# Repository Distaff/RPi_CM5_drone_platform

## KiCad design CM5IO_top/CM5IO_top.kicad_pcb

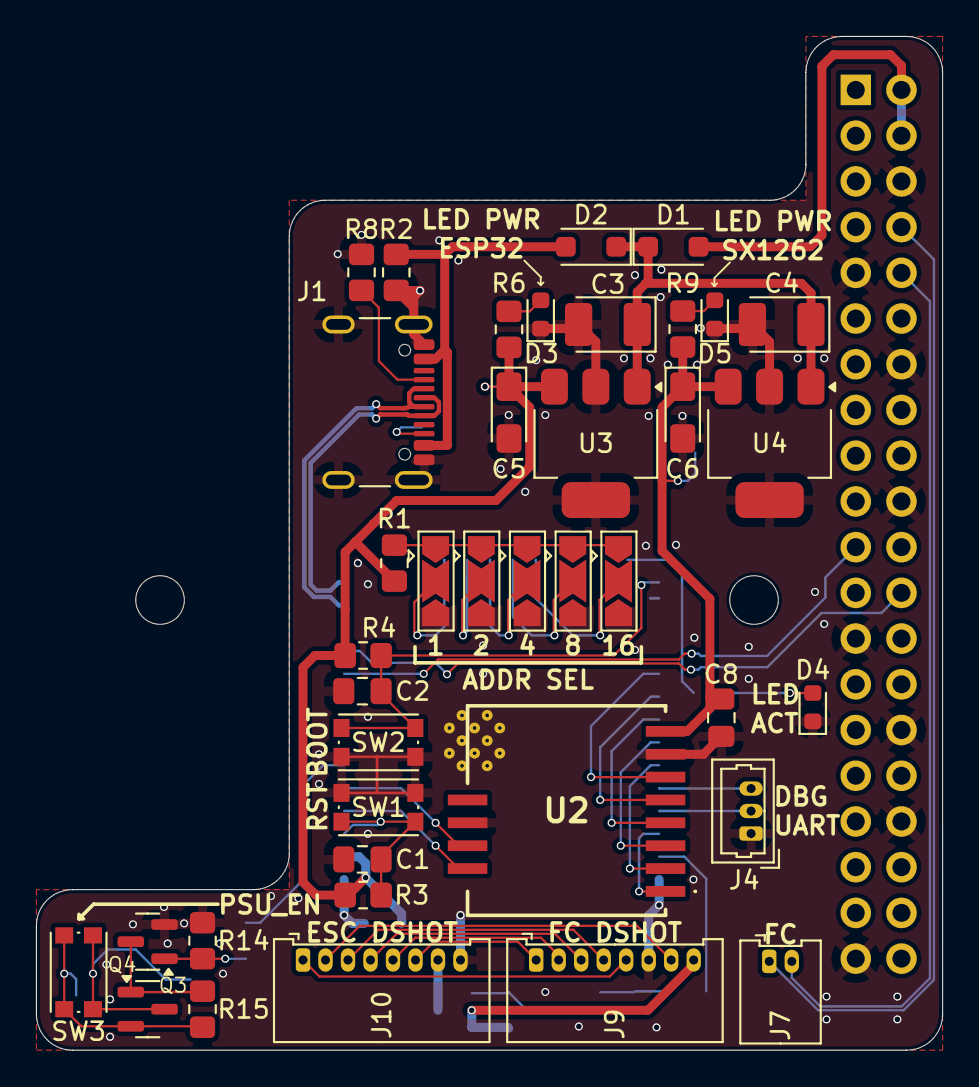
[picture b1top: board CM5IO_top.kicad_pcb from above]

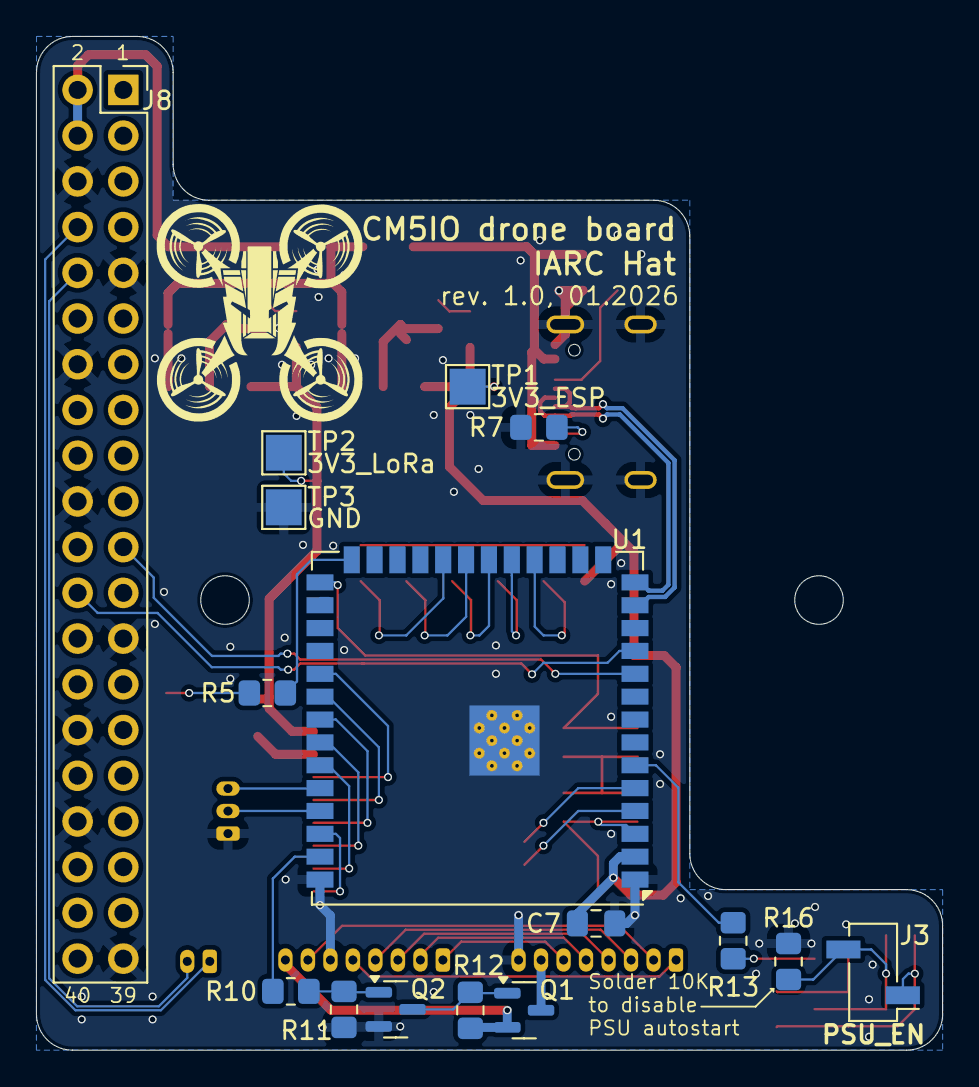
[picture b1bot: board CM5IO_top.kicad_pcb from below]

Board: 2 copper layers, 50.3 x 56.3 mm, 58 parts (16 on the bottom side), 52 nets.

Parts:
C1, C2, C7, C8: 470nF; C_0805_2012Metric_Pad1.18x1.45mm_HandSolder
C3, C4: 4.7uF 35v; CP_EIA-3528-21_Kemet-B_HandSolder
C5, C6: 4.7uF 10v; CP_EIA-3216-18_Kemet-A_HandSolder
D1, D2: MBR1020VL; D_SOD-123F
D3, D5: LED Red; LED_0603_1608Metric
D4: LED Green; LED_0603_1608Metric
H1, H2: MountingHole; MountingHole_2.7mm_M2.5_DIN965
J1: USB_C_Receptacle_USB2.0; USB_C_Receptacle_GCT_USB4105-xx-A_16P_TopMnt_Horizontal
J3: J_PSU_EN; PinSocket_1x02_P2.54mm_Vertical_SMD_Pin1Left
J4: J_ESP_DBG_UART; Molex_PicoBlade_53047-0310_1x03_P1.25mm_Vertical
J7: J_FC_UART; Molex_PicoBlade_53048-0210_1x02_P1.25mm_Horizontal
J8: THD-20-R; PinSocket_2x20_P2.54mm_Vertical
J9: J_DShot600_ESC; Molex_PicoBlade_53048-0810_1x08_P1.25mm_Horizontal
J10: J_DShot600_FC; Molex_PicoBlade_53048-0810_1x08_P1.25mm_Horizontal
JP1: ADDR1; SolderJumper-3_P2.0mm_Open_TrianglePad1.0x1.5mm
JP2: ADDR2; SolderJumper-3_P2.0mm_Open_TrianglePad1.0x1.5mm
JP3: ADDR4; SolderJumper-3_P2.0mm_Open_TrianglePad1.0x1.5mm
JP4: ADDR8; SolderJumper-3_P2.0mm_Open_TrianglePad1.0x1.5mm
JP5: ADDR16; SolderJumper-3_P2.0mm_Open_TrianglePad1.0x1.5mm
Module1: ComputeModule5-CM5; Raspberry-Pi-5-Compute-Module
Q1, Q4: AO3401A; SOT-23
Q2, Q3: Q_NPN_BEC; SOT-23
R1, R3, R4, R5, R6, R9, R10, R12, R13, R15: 1K; R_0805_2012Metric_Pad1.20x1.40mm_HandSolder
R2: 2.2K 1%; R_0805_2012Metric_Pad1.20x1.40mm_HandSolder
R7, R8: 5.1K 1%; R_0805_2012Metric_Pad1.20x1.40mm_HandSolder
R11, R14, R16: 10K; R_0805_2012Metric_Pad1.20x1.40mm_HandSolder
SW1: SW_RESET; SW_Push_1P1T_NO_CK_KMR2
SW2: SW_BOOT; SW_Push_1P1T_NO_CK_KMR2
SW3: FORCE_PWR; SW_Push_1P1T_NO_CK_KMR2
TP1: 3V3_ESP; TestPoint_Pad_2.0x2.0mm
TP2: 3V3_LORA; TestPoint_Pad_2.0x2.0mm
TP3: GND; TestPoint_Pad_2.0x2.0mm
U1: ESP32-S3-WROOM-1; ESP32-S3-WROOM-1U
U2: Wio-SX1262
U3, U4: AP7361C-33E; SOT-223-3_TabPin2

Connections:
/+3.3v_ESP: C5.1, C7.2, R1.1, R3.1, R4.1, R6.1, TP1.1, U1.2 (3V3), U3.3 (VO)
/+3.3v_LoRa: C6.1, C8.2, R9.1, TP2.1, U2.8 (VCC), U4.3 (VO)
/+5v_RPi: D1.2 (A), J8.2, J8.4
/+5v_USB: D2.2 (A), J1.A4 (VBUS), J1.A9 (VBUS), J1.B4 (VBUS), J1.B9 (VBUS), R2.1
/Comm/ADDR1: JP1.2 (C), U1.18 (IO10)
/Comm/ADDR2: JP2.2 (C), U1.19 (IO11)
/Comm/ADDR4: JP3.2 (C), U1.20 (IO12)
/Comm/ADDR8: JP4.2 (C), U1.21 (IO13)
/Comm/ADDR16: JP5.2 (C), U1.22 (IO14)
/Comm/ADDR_HIGH: JP1.1 (A), JP2.1 (A), JP3.1 (A), JP4.1 (A), JP5.1 (A), R1.2
/Comm/BOOT_MODE: C2.2, R4.2, SW2.2, U1.27 (IO0)
/Comm/ENABLE: C1.2, R3.2, SW1.2, U1.3 (EN)
/Comm/KILLSWITCH_FC_CTL: R10.1, U1.39 (IO1)
/Comm/KILLSWITCH_PSU_CTL: R13.1, U1.6 (IO6)
/Comm/LED_ACT: R5.1, U1.26 (IO45)
/Comm/LORA_BUSY: U1.5 (IO5), U2.11 (BUSY)
/Comm/LORA_DIO1: U1.4 (IO4), U2.12 (DIO1)
/Comm/LORA_RESET: U1.32 (IO39), U2.5 (NRST)
/Comm/LORA_RF_SW: U1.38 (IO2), U2.1 (RF_SW_)
/Comm/LORA_SPI_CLK: U1.33 (IO40), U2.4 (SCK)
/Comm/LORA_SPI_CS: U1.31 (IO38), U2.6 (NSS)
/Comm/LORA_SPI_MISO: U1.35 (IO42), U2.2 (MISO)
/Comm/LORA_SPI_MOSI: U1.34 (IO41), U2.3 (MOSI)
/Dshot600_CURR: J9.5, J10.1
/Dshot600_M1: J9.4, J10.3
/Dshot600_M2: J9.3, J10.4
/Dshot600_M3: J9.2, J10.5
/Dshot600_M4: J9.1, J10.6
/Dshot600_R7: J9.7, J10.2
/ESP_USB2_N: J1.A7 (D-), J1.B7 (D-), U1.13 (USB_D-)
/ESP_USB2_P: J1.A6 (D+), J1.B6 (D+), U1.14 (USB_D+)
/GPIO8: J8.24, U1.11 (IO18)
/GPIO9: J8.21, U1.10 (IO17)
/GPIO14_UART_TX: J7.1, J8.8
/GPIO15_UART_RX: J7.2, J8.10
/PSU_CTL_EN: J3.2, Q4.3 (D), R16.1, SW3.1
/PSU_VIN: J3.1, Q4.2 (S), R15.1, SW3.2
/VBUS_ESC: J9.8, Q1.2 (S), R12.1
/VBUS_FC: J10.7, Q1.3 (D)
/VIN: C3.1, C4.1, D1.1 (K), D2.1 (K), U3.1 (VI), U4.1 (VI)
GND: C1.1, C2.1, C3.2, C4.2, C5.2, C6.2, C7.1, C8.1, D3.1 (K), D4.1 (K), D5.1 (K), J1.A1 (GND), J1.A12 (GND), J1.B1 (GND), J1.B12 (GND), J1.S1 (SHIELD), J4.1, J8.6, J8.9, J8.14, J8.20, J8.25, J8.30, J8.34, J8.39, J9.6, J10.8, JP1.3 (B), JP2.3 (B), JP3.3 (B), JP4.3 (B), JP5.3 (B), Q2.2 (E), Q3.2 (E), R2.2, R7.1, R8.1, R11.2, R14.2, R16.2, SW1.1, SW2.1, TP3.1, U1.1 (GND), U1.40 (GND), U1.41 (GND), U2.7 (GND_1), U2.10 (GND_2), U3.2 (GND), U4.2 (GND)
unnamed: D3.2 (A), R6.2
unnamed: D4.2 (A), R5.2
unnamed: D5.2 (A), R9.2
unnamed: J1.A5 (CC1), R8.2
unnamed: J1.B5 (CC2), R7.2
unnamed: J4.2, U1.37 (TXD0)
unnamed: J4.3, U1.36 (RXD0)
unnamed: Q1.1 (G), Q2.3 (C), R12.2
unnamed: Q2.1 (B), R10.2, R11.1
unnamed: Q3.1 (B), R13.2, R14.1
unnamed: Q3.3 (C), Q4.1 (G), R15.2

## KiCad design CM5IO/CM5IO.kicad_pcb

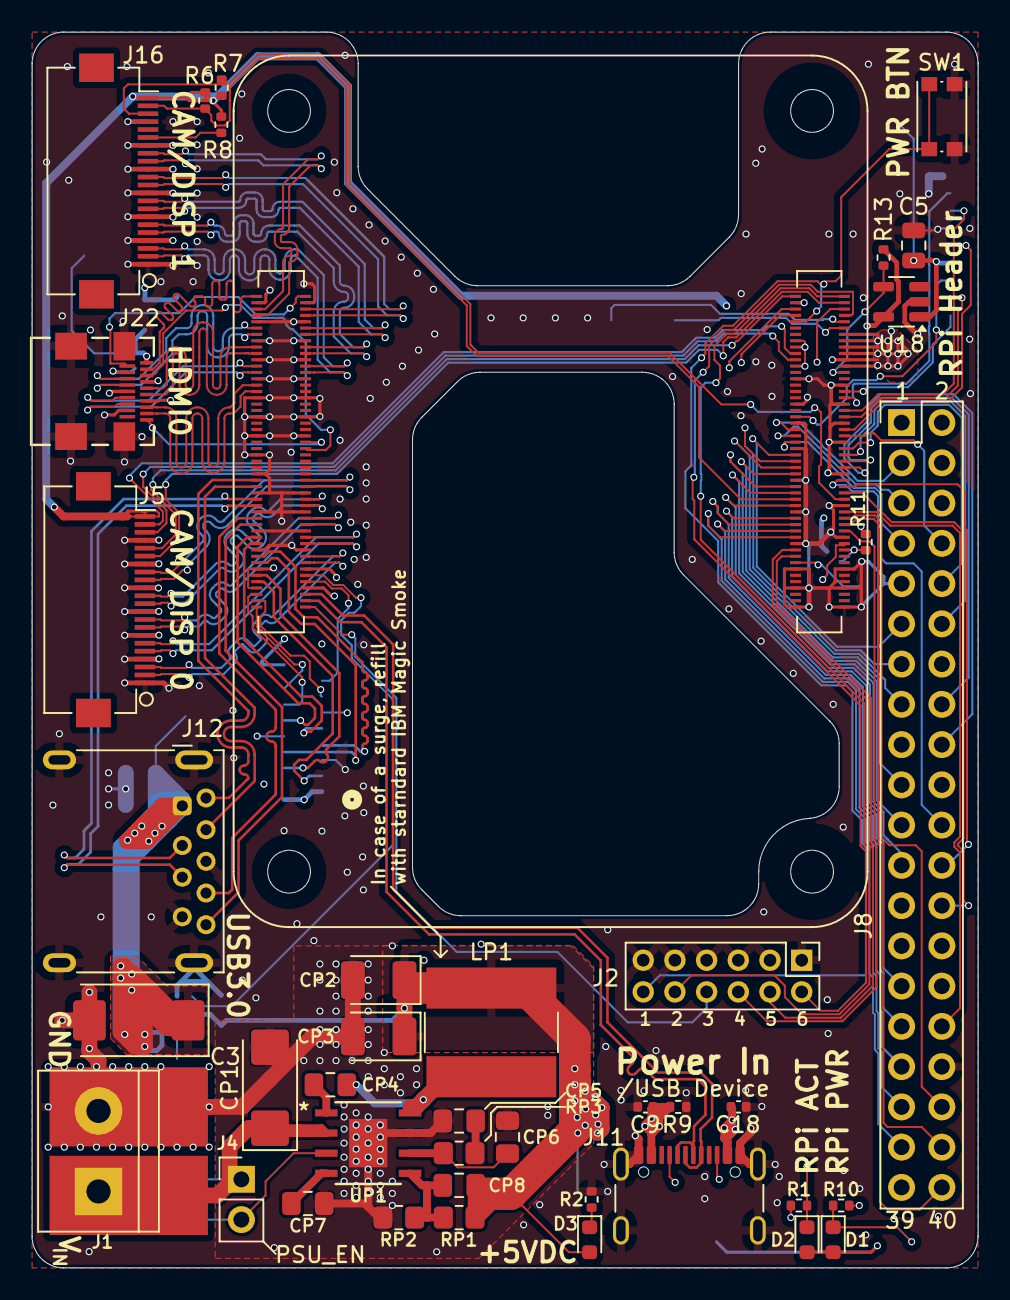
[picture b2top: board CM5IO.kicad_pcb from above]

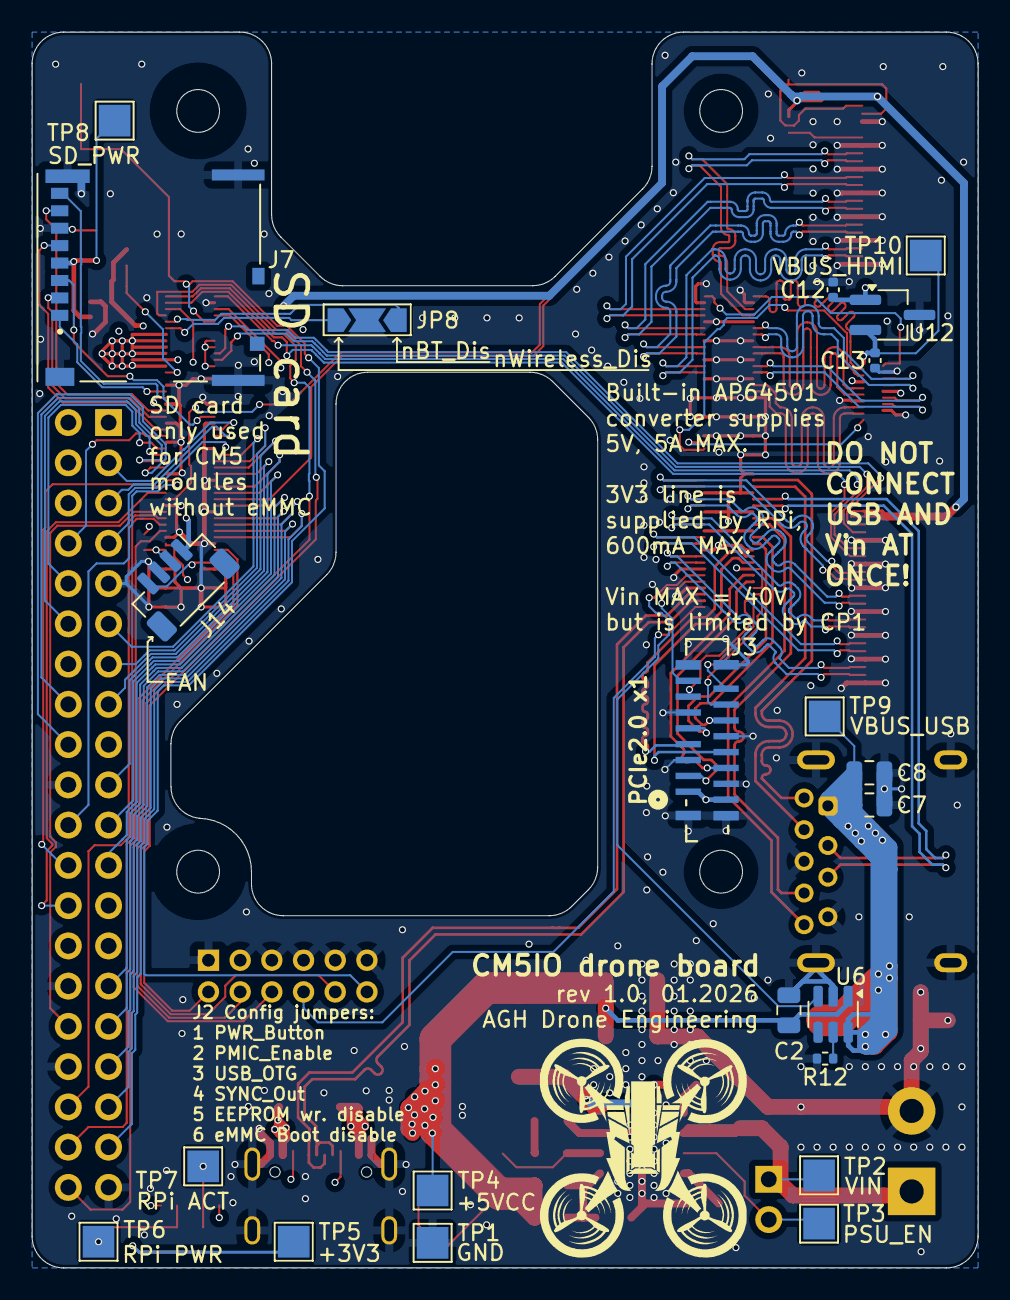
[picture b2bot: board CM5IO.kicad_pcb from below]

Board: 4 copper layers, 59.7 x 78.0 mm, 65 parts (22 on the bottom side), 123 nets.

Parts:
C2, C5, C7, C8: 10u; C_0805_2012Metric
C3: 100uF; CP_EIA-7343-31_Kemet-D
C9, C12, C13, C18: 100n; C_0402_1005Metric
CP1: 10uF; CP_EIA-6032-28_Kemet-C_HandSolder
CP2, CP3: 22uF; CP_EIA-3528-21_Kemet-B_HandSolder
CP4: 100nF; C_0805_2012Metric_Pad1.18x1.45mm_HandSolder
CP5: 2.7nF; C_0805_2012Metric_Pad1.18x1.45mm_HandSolder
CP6: 33pF; C_0805_2012Metric_Pad1.18x1.45mm_HandSolder
CP7: 10nF; C_0805_2012Metric_Pad1.18x1.45mm_HandSolder
CP8: OPEN; C_0805_2012Metric_Pad1.18x1.45mm_HandSolder
D1, D3: LED Red; LED_0603_1608Metric
D2: LED Green; LED_0603_1608Metric
H9: VIN_SOLDERPOINT; SolderWirePad_1x01_SMD_5x10mm
H10: GND_SOLDERPOINT; SolderWirePad_1x01_SMD_5x10mm
J1: POWER TERMINAL; TerminalBlock_bornier-2_P5.08mm
J2: Conn_02x06_Odd_Even; PinHeader_2x06_P2.00mm_Vertical
J3: 62674-161121ALF; CON16_1X16_DUT_58XF_GLE
J4: J_PSU_EN; PinHeader_1x02_P2.54mm_Vertical
J5, J16: Conn_01x22_Female; Hirose_FH12-22S-0.5SH_1x22-1MP_P0.50mm_Horizontal
J7: Micro_SD_Card_Det; SDCARD_MOLEX_503398-1892
J8: THD-20-R; PinHeader_2x20_P2.54mm_Vertical
J11: USB_C_Receptacle_USB2.0; USB_C_Receptacle_GCT_USB4105-xx-A_16P_TopMnt_Horizontal
J12: USB3_A; USB3_A_Molex_48393-001
J14: JST_SHBM04B-SRSS-TB; JST_SH_BM04B-SRSS-TB_1x04-1MP_P1.00mm_Vertical
J22: 46765-1301; CONN_467651301_MOL
JP8: BT_WIFI_DISABLE; SolderJumper-3_P2.0mm_Open_TrianglePad1.0x1.5mm
LP1: 3.6uH; L_Bourns-SRN8040_8x8.15mm
Module1: ComputeModule5-CM5; Raspberry-Pi-5-Compute-Module
R1, R2, R10: 1k; R_0402_1005Metric
R6, R7, R8, R9: 2.2K 1%; R_0402_1005Metric
R11, R13: 10K 1%; R_0402_1005Metric
R12: 15K 1%; R_0402_1005Metric
RP1: 115K; R_0805_2012Metric_Pad1.20x1.40mm_HandSolder
RP2: 22.1K; R_0805_2012Metric_Pad1.20x1.40mm_HandSolder
RP3: 15.8K; R_0805_2012Metric_Pad1.20x1.40mm_HandSolder
SW1: Right angle Tact button; SW_Push_1P1T_NO_CK_KMR2
TP1: TP GND; TestPoint_Pad_2.0x2.0mm
TP2: TP VIN; TestPoint_Pad_2.0x2.0mm
TP3: TP PSU_EN; TestPoint_Pad_2.0x2.0mm
TP4: TP +5VCC; TestPoint_Pad_2.0x2.0mm
TP5: TP +3V3; TestPoint_Pad_2.0x2.0mm
TP6: TP nPWR; TestPoint_Pad_2.0x2.0mm
TP7: TP nACT; TestPoint_Pad_2.0x2.0mm
TP8: TP SD_PWR; TestPoint_Pad_2.0x2.0mm
TP9: TP VBUS_USB; TestPoint_Pad_2.0x2.0mm
TP10: TP VBUS_HDMI; TestPoint_Pad_2.0x2.0mm
U6: AP22653W6; SOT-23-6
U12: RT9742SNGV; TSOT-23_HandSoldering
U18: RT9742GGJ5; SOT-23-5
UP1: AP64501SP-13; SOP_AP64501SP-13_DIO

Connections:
/+3.3v: D1.2 (A), D2.2 (A), J5.22, J8.1, J8.17, J16.22, Module1.78 (GPIO_VREF(1.8v/3.3v_Input)), Module1.84 (+3.3v_(Output)), Module1.86 (+3.3v_(Output)), R6.1, R7.1, R8.1, R11.1, R13.1, TP5.1, U18.5 (IN)
/+5v: C2.1, C9.1, C12.1, C18.1, CP2.1, CP3.1, CP8.1, D3.2 (A), J3.1, J3.2, J8.2, J8.4, J11.A4 (VBUS), J11.A9 (VBUS), J11.B4 (VBUS), J11.B9 (VBUS), J14.1, LP1.2, Module1.77 (+5v_(Input)), Module1.79 (+5v_(Input)), Module1.81 (+5v_(Input)), Module1.83 (+5v_(Input)), Module1.85 (+5v_(Input)), Module1.87 (+5v_(Input)), R9.1, RP1.1, TP4.1, U6.1 (IN), U12.1 (IN)
/CC1: J11.A5 (CC1), Module1.94 (CC1)
/CC2: J11.B5 (CC2), Module1.96 (CC2)
/CM5_GPIO ( Ethernet, GPIO, SDCARD)/BT_nDis: JP8.3 (B), Module1.91 (BT_nDisable)
/CM5_GPIO ( Ethernet, GPIO, SDCARD)/CAM_GPIO0: J5.17, Module1.97 (CAM_GPIO0)
/CM5_GPIO ( Ethernet, GPIO, SDCARD)/CAM_GPIO1: J5.18, Module1.100 (CAM_GPIO1)
/CM5_GPIO ( Ethernet, GPIO, SDCARD)/EEPROM_nWP: J2.4, Module1.20 (EEPROM_nWP)
/CM5_GPIO ( Ethernet, GPIO, SDCARD)/GPIO2: J8.3, Module1.58 (GPIO2)
/CM5_GPIO ( Ethernet, GPIO, SDCARD)/GPIO3: J8.5, Module1.56 (GPIO3)
/CM5_GPIO ( Ethernet, GPIO, SDCARD)/GPIO4: J8.7, Module1.54 (GPIO4)
/CM5_GPIO ( Ethernet, GPIO, SDCARD)/GPIO5: J8.29, Module1.34 (GPIO5)
/CM5_GPIO ( Ethernet, GPIO, SDCARD)/GPIO6: J8.31, Module1.30 (GPIO6)
/CM5_GPIO ( Ethernet, GPIO, SDCARD)/GPIO7: J8.26, Module1.37 (GPIO7)
/CM5_GPIO ( Ethernet, GPIO, SDCARD)/GPIO8: J8.24, Module1.39 (GPIO8)
/CM5_GPIO ( Ethernet, GPIO, SDCARD)/GPIO9: J8.21, Module1.40 (GPIO9)
/CM5_GPIO ( Ethernet, GPIO, SDCARD)/GPIO10: J8.19, Module1.44 (GPIO10)
/CM5_GPIO ( Ethernet, GPIO, SDCARD)/GPIO11: J8.23, Module1.38 (GPIO11)
/CM5_GPIO ( Ethernet, GPIO, SDCARD)/GPIO12: J8.32, Module1.31 (GPIO12)
/CM5_GPIO ( Ethernet, GPIO, SDCARD)/GPIO13: J8.33, Module1.28 (GPIO13)
/CM5_GPIO ( Ethernet, GPIO, SDCARD)/GPIO14: J8.8, Module1.55 (GPIO14)
/CM5_GPIO ( Ethernet, GPIO, SDCARD)/GPIO15: J8.10, Module1.51 (GPIO15)
/CM5_GPIO ( Ethernet, GPIO, SDCARD)/GPIO16: J8.36, Module1.29 (GPIO16)
/CM5_GPIO ( Ethernet, GPIO, SDCARD)/GPIO17: J8.11, Module1.50 (GPIO17)
/CM5_GPIO ( Ethernet, GPIO, SDCARD)/GPIO18: J8.12, Module1.49 (GPIO18)
/CM5_GPIO ( Ethernet, GPIO, SDCARD)/GPIO19: J8.35, Module1.26 (GPIO19)
/CM5_GPIO ( Ethernet, GPIO, SDCARD)/GPIO20: J8.38, Module1.27 (GPIO20)
/CM5_GPIO ( Ethernet, GPIO, SDCARD)/GPIO21: J8.40, Module1.25 (GPIO21)
/CM5_GPIO ( Ethernet, GPIO, SDCARD)/GPIO22: J8.15, Module1.46 (GPIO22)
/CM5_GPIO ( Ethernet, GPIO, SDCARD)/GPIO23: J8.16, Module1.47 (GPIO23)
/CM5_GPIO ( Ethernet, GPIO, SDCARD)/GPIO24: J8.18, Module1.45 (GPIO24)
/CM5_GPIO ( Ethernet, GPIO, SDCARD)/GPIO25: J8.22, Module1.41 (GPIO25)
/CM5_GPIO ( Ethernet, GPIO, SDCARD)/GPIO26: J8.37, Module1.24 (GPIO26)
/CM5_GPIO ( Ethernet, GPIO, SDCARD)/GPIO27: J8.13, Module1.48 (GPIO27)
/CM5_GPIO ( Ethernet, GPIO, SDCARD)/PMIC_ENABLE: J2.10, Module1.99 (PMIC_ENABLE)
/CM5_GPIO ( Ethernet, GPIO, SDCARD)/PWM: J14.2, Module1.19 (FAN_PWM), R11.2
/CM5_GPIO ( Ethernet, GPIO, SDCARD)/PWR_BUT: J2.12, Module1.92 (PWR_BUT), SW1.1
/CM5_GPIO ( Ethernet, GPIO, SDCARD)/SD_CLK: J7.5 (CLK), Module1.57 (SD_CLK)
/CM5_GPIO ( Ethernet, GPIO, SDCARD)/SD_CMD: J7.3 (CMD), Module1.62 (SD_CMD)
/CM5_GPIO ( Ethernet, GPIO, SDCARD)/SD_DAT0: J7.7 (DAT0), Module1.63 (SD_DAT0)
/CM5_GPIO ( Ethernet, GPIO, SDCARD)/SD_DAT1: J7.8 (DAT1), Module1.67 (SD_DAT1)
/CM5_GPIO ( Ethernet, GPIO, SDCARD)/SD_DAT2: J7.1 (DAT2), Module1.69 (SD_DAT2)
/CM5_GPIO ( Ethernet, GPIO, SDCARD)/SD_DAT3: J7.2 (DAT3/CD), Module1.61 (SD_DAT3)
/CM5_GPIO ( Ethernet, GPIO, SDCARD)/SD_PWR: C5.1, J7.4 (VDD), TP8.1, U18.1 (OUT)
/CM5_GPIO ( Ethernet, GPIO, SDCARD)/SD_PWR_ON: Module1.75 (SD_PWR_ON), R13.2, U18.4 (EN)
/CM5_GPIO ( Ethernet, GPIO, SDCARD)/SYNC_OUT: J2.6, Module1.18 (Ethernet_SYNC_OUT(3.3v))
/CM5_GPIO ( Ethernet, GPIO, SDCARD)/TACHO: J14.4, Module1.16 (FAN_TACHO)
/CM5_GPIO ( Ethernet, GPIO, SDCARD)/USBOTG: J2.8, Module1.101 (USB_OTG_ID)
/CM5_GPIO ( Ethernet, GPIO, SDCARD)/WL_nDis: JP8.1 (A), Module1.89 (WiFi_nDisable)
/CM5_GPIO ( Ethernet, GPIO, SDCARD)/nPWR_LED: Module1.95 (LED_nPWR), R10.2
/CM5_GPIO ( Ethernet, GPIO, SDCARD)/nRPIBOOT: J2.2, Module1.93 (nRPIBOOT)
/CM5_HighSpeed/DPHY0_C_N: J5.8, Module1.127 (MIPI0_C_N)
/CM5_HighSpeed/DPHY0_C_P: J5.9, Module1.129 (MIPI0_C_P)
/CM5_HighSpeed/DPHY0_D0_N: J5.2, Module1.115 (MIPI0_D0_N)
/CM5_HighSpeed/DPHY0_D0_P: J5.3, Module1.117 (MIPI0_D0_P)
/CM5_HighSpeed/DPHY0_D1_N: J5.5, Module1.121 (MIPI0_D1_N)
/CM5_HighSpeed/DPHY0_D1_P: J5.6, Module1.123 (MIPI0_D1_P)
/CM5_HighSpeed/DPHY0_D2_N: J5.11, Module1.133 (MIPI0_D2_N)
/CM5_HighSpeed/DPHY0_D2_P: J5.12, Module1.135 (MIPI0_D2_P)
/CM5_HighSpeed/DPHY0_D3_N: J5.14, Module1.139 (MIPI0_D3_N)
/CM5_HighSpeed/DPHY0_D3_P: J5.15, Module1.141 (MIPI0_D3_P)
/CM5_HighSpeed/DPHY1_C_N: J16.8, Module1.187 (MIPI1_C_N)
/CM5_HighSpeed/DPHY1_C_P: J16.9, Module1.189 (MIPI1_C_P)
/CM5_HighSpeed/DPHY1_D0_N: J16.2, Module1.175 (MIPI1_D0_N)
/CM5_HighSpeed/DPHY1_D0_P: J16.3, Module1.177 (MIPI1_D0_P)
/CM5_HighSpeed/DPHY1_D1_N: J16.5, Module1.181 (MIPI1_D1_N)
/CM5_HighSpeed/DPHY1_D1_P: J16.6, Module1.183 (MIPI1_D1_P)
/CM5_HighSpeed/DPHY1_D2_N: J16.11, Module1.193 (MIPI1_D2_N)
/CM5_HighSpeed/DPHY1_D2_P: J16.12, Module1.195 (MIPI1_D2_P)
/CM5_HighSpeed/DPHY1_D3_N: J16.14, Module1.194 (MIPI1_D3_N)
/CM5_HighSpeed/DPHY1_D3_P: J16.15, Module1.196 (MIPI1_D3_P)
/CM5_HighSpeed/HDMI0_CEC: J22.15 (CEC), Module1.151 (HDMI0_CEC)
/CM5_HighSpeed/HDMI0_CK_N: J22.14 (CK-), Module1.190 (HDMI0_CLK_N)
/CM5_HighSpeed/HDMI0_CK_P: J22.12 (CK+), Module1.188 (HDMI0_CLK_P)
/CM5_HighSpeed/HDMI0_D0_N: J22.11 (D0-), Module1.184 (HDMI0_TX0_N)
/CM5_HighSpeed/HDMI0_D0_P: J22.9 (D0+), Module1.182 (HDMI0_TX0_P)
/CM5_HighSpeed/HDMI0_D1_N: J22.8 (D1-), Module1.178 (HDMI0_TX1_N)
/CM5_HighSpeed/HDMI0_D1_P: J22.6 (D1+), Module1.176 (HDMI0_TX1_P)
/CM5_HighSpeed/HDMI0_D2_N: J22.5 (D2-), Module1.172 (HDMI0_TX2_N)
/CM5_HighSpeed/HDMI0_D2_P: J22.3 (D2+), Module1.170 (HDMI0_TX2_P)
/CM5_HighSpeed/HDMI0_HOTPLUG: J22.1 (HPD/HEAC-), Module1.153 (HDMI0_HOTPLUG)
/CM5_HighSpeed/HDMI0_SCL: J22.17 (SCL), Module1.200 (HDMI0_SCL)
/CM5_HighSpeed/HDMI0_SDA: J22.18 (SDA), Module1.199 (HDMI0_SDA)
/CM5_HighSpeed/HDMI_5v: C13.1, J22.19 (+5V), TP10.1, U12.2 (OUT)
/CM5_HighSpeed/PCIE_CLKREQ_N: J3.15, Module1.102 (PCIe_nCLKREQ)
/CM5_HighSpeed/PCIE_CLK_N: J3.5, Module1.112 (PCIe_CLK_N)
/CM5_HighSpeed/PCIE_CLK_P: J3.4, Module1.110 (PCIe_CLK_P)
/CM5_HighSpeed/PCIE_DET_WAKE: J3.14, Module1.104 (PCIE_nWAKE)
/CM5_HighSpeed/PCIE_PWR_EN: J3.13, Module1.106 (PCIE_PWR_EN)
/CM5_HighSpeed/PCIE_RST_B: J3.16, Module1.109 (PCIe_nRST)
/CM5_HighSpeed/PCIE_RX_N: J3.8, Module1.118 (PCIe_RX_N)
/CM5_HighSpeed/PCIE_RX_P: J3.7, Module1.116 (PCIe_RX_P)
/CM5_HighSpeed/PCIE_TX_N: J3.11, Module1.124 (PCIe_TX_N)
/CM5_HighSpeed/PCIE_TX_P: J3.10, Module1.122 (PCIe_TX_P)
/CM5_HighSpeed/SCL0: J5.20, Module1.80 (SCL0)
/CM5_HighSpeed/SCL1: J16.20, Module1.35 (ID_SC), R7.2
/CM5_HighSpeed/SDA0: J5.21, Module1.82 (SDA0)
/CM5_HighSpeed/SDA1: J16.21, Module1.36 (ID_SD), R6.2
/CM5_HighSpeed/USB3-0-D_N: J12.2 (D-), Module1.136 (USB3-0-D_N)
/CM5_HighSpeed/USB3-0-D_P: J12.3 (D+), Module1.134 (USB3-0-D_P)
/CM5_HighSpeed/USB3-0-RX_N: J12.5 (SSRX-), Module1.128 (USB3-0-RX_N)
/CM5_HighSpeed/USB3-0-RX_P: J12.6 (SSRX+), Module1.130 (USB3-0-RX_P)
/CM5_HighSpeed/USB3-0-TX_N: J12.8 (SSTX-), Module1.140 (USB3-0-TX_N)
/CM5_HighSpeed/USB3-0-TX_P: J12.9 (SSTX+), Module1.142 (USB3-0-TX_P)
/CM5_HighSpeed/VBUS: C3.1, C7.1, C8.1, J12.1 (VBUS), TP9.1, U6.6 (OUT)
/CM5_HighSpeed/VBUS_EN: Module1.111 (VBUS_EN), U6.3 (EN)
/PSU/PSU_EN: J4.2, TP3.1, UP1.3 (EN)
/PSU/SW: CP4.2, LP1.1, UP1.8 (SW)
/USB2_N: J11.A7 (D-), J11.B7 (D-), Module1.103 (USB2_N)
/USB2_P: J11.A6 (D+), J11.B6 (D+), Module1.105 (USB2_P)
/VIN: CP1.1, H9.1 (MP), J1.1, J4.1, TP2.1, UP1.2 (VIN)
GND: C2.2, C3.2, C5.2, C7.2, C8.2, C9.2, C12.2, C13.2, C18.2, CP1.2, CP2.2, CP3.2, CP5.2, CP6.2, CP7.1, H10.1 (MP), J1.2, J2.1, J2.3, J2.5, J2.7, J2.9, J2.11, J3.3, J3.6, J3.9, J3.12, J3.SH1, J3.SH2, J3.SH3, J3.SH4, J5.1, J5.4, J5.7, J5.10, J5.13, J5.16, J5.19, J7.6 (VSS), J7.11 (SHIELD), J8.6, J8.9, J8.14, J8.20, J8.25, J8.30, J8.34, J8.39, J11.A1 (GND), J11.A12 (GND), J11.B1 (GND), J11.B12 (GND), J11.S1 (SHIELD), J12.4 (GND), J12.7 (DRAIN), J12.10 (SHIELD), J14.3, J16.1, J16.4, J16.7, J16.10, J16.13, J16.16, J16.19, J22.4 (D2S), J22.7 (D1S), J22.10 (D0S), J22.13 (CKS), J22.16 (GND), J22.SH, JP8.2 (C), Module1.1 (GND), Module1.2 (GND), Module1.7 (GND), Module1.8 (GND), Module1.13 (GND), Module1.14 (GND), Module1.22 (GND), Module1.23 (GND), Module1.32 (GND), Module1.33 (GND), Module1.42 (GND), Module1.43 (GND), Module1.52 (GND), Module1.53 (GND), Module1.59 (GND), Module1.60 (GND), Module1.65 (GND), Module1.66 (GND), Module1.71 (GND), Module1.74 (GND), Module1.98 (GND), Module1.107 (GND), Module1.108 (GND), Module1.113 (GND), Module1.114 (GND), Module1.119 (GND), Module1.120 (GND), Module1.125 (GND), Module1.126 (GND), Module1.131 (GND), Module1.132 (GND), Module1.137 (GND), Module1.138 (GND), Module1.144 (GND), Module1.150 (GND), Module1.155 (GND), Module1.156 (GND), Module1.161 (GND), Module1.162 (GND), Module1.167 (GND), Module1.168 (GND), Module1.173 (GND), Module1.174 (GND), Module1.179 (GND), Module1.180 (GND), Module1.185 (GND), Module1.186 (GND), Module1.191 (GND), Module1.192 (GND), Module1.197 (GND), Module1.198 (GND), R2.2, R9.2, R12.2, RP2.2, SW1.2, TP1.1, U6.2 (GND), U12.3 (GND), U18.2 (GND), UP1.7 (GND), UP1.9 (EP)
unnamed: CP5.1, RP3.2
unnamed: D1.1 (K), R10.1, TP6.1
unnamed: D2.1 (K), R1.1, TP7.1
unnamed: D3.1 (K), R2.1
unnamed: J16.17, R8.2
unnamed: Module1.21 (LED_nACT), R1.2
unnamed: R12.1, U6.5 (ILIM)
unnamed: CP4.1, UP1.1 (BST)
unnamed: CP6.1, RP3.1, UP1.6 (COMP)
unnamed: CP8.2, RP1.2, RP2.1, UP1.5 (FB)
unnamed: CP7.2, UP1.4 (SS)

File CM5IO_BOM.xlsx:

Qty/ board | Ref | Value | Footprint | Desc | Part No. | MOUSER |  | Farnell |  | TME
 |  |  |  |  |  | Unit Price | Code | Unit Price | Code | Unit Price | Code | min. Il. na 10 płytek
4 | C9,C12,C13,C18 | 100n | Capacitor_SMD:C_0402_1005Metric | 0.1uF 10% 16V Ceramic Capacitor X7R 0402 (1005 Metric) | - |  |  |  |  | 3.9190000000000003E-2 | 04025C104KAT2A | 12 | 0.47028000000000003
1 | CP6 | 33pF | Capacitor_SMD:C_0805_2012Metric_Pad1.18x1.45mm_HandSolder | - | - |  |  |  |  | 0.20480000000000001 | 08055A330KAT2A | 12 | 2.4576000000000002
1 | CP5 | 2.7nF | Capacitor_SMD:C_0805_2012Metric_Pad1.18x1.45mm_HandSolder | - | - |  |  |  |  | 0.18210000000000001 | 08055C272KAT2A | 12 | 2.1852
1 | CP7 | 10nF | Capacitor_SMD:C_0805_2012Metric_Pad1.18x1.45mm_HandSolder | - | - |  |  |  |  | 0.1421 | 08055C103KAT2A | 12 | 1.7052
1 | CP4 | 100nF | Capacitor_SMD:C_0805_2012Metric_Pad1.18x1.45mm_HandSolder | - | - |  |  |  |  | 4.1669999999999999E-2 | 08055C104KAT2A | 12 | 0.50004000000000004
4 | C2,C5,C7,C8 | 10u | Capacitor_SMD:C_0805_2012Metric | 10uF 10% 10V Ceramic Capacitor X7R 0805 (2012 Metric) | - |  |  |  |  | 0.28220000000000001 | 08055C105KAT2A | 42 | 11.852399999999999
3 | R1,R2,R10 | 1k | Resistor_SMD:R_0402_1005Metric | Resistor 1K M1005 1% 63mW | - |  |  |  |  | 3.3119999999999997E-2 | SMD0402-1K-1% | 100 | 3.3119999999999998
4 | R6,R7,R8,R9 | 2.2K 1% | Resistor_SMD:R_0402_1005Metric | Resistor 2.2K M1005 1% 63mW | - |  |  |  |  | 3.9050000000000001E-2 | SMD0402-2K2-1% | 100 | 3.9050000000000002
2 | R11,R13 | 10K 1% | Resistor_SMD:R_0402_1005Metric | Resistor 10K M1005 1% 63mW | - |  |  |  |  | 1.7569999999999999E-2 | SMD0402-10K-1% | 100 | 1.7569999999999999
1 | R12 | 15K 1% | Resistor_SMD:R_0402_1005Metric | Resistor 15K M1005 1% 63mW | - |  |  |  |  | 3.6560000000000002E-2 | SMD0402-15K-1% | 100 | 3.6560000000000001
1 | RP1 | 115K | Resistor_SMD:R_0805_2012Metric_Pad1.20x1.40mm_HandSolder | - | - |  |  |  |  | 0.21560000000000001 | ERA6AEB1153V | 12 | 2.5872000000000002
1 | RP2 | 22.1K | Resistor_SMD:R_0805_2012Metric_Pad1.20x1.40mm_HandSolder | - | - |  |  |  |  | 5.9389999999999998E-2 | SMD0805-22K1-1% | 100 | 5.9390000000000001
1 | RP3 | 15.8K | Resistor_SMD:R_0805_2012Metric_Pad1.20x1.40mm_HandSolder | - | - |  |  |  |  | 6.7129999999999995E-2 | SMD0805-15.8K-1% | 100 | 6.7129999999999992
1 | J1 | POWER TERMINAL | TerminalBlock:TerminalBlock_bornier-2_P5.08mm | - | -
1 | J2 | Conn_02x06_Odd_Even | Connector_PinHeader_2.00mm:PinHeader_2x06_P2.00mm_Vertical | PinHeader_2x06_P2.54mm_Vertical | -
1 | J4 | J_PSU_EN | Connector_PinHeader_2.54mm:PinHeader_1x02_P2.54mm_Vertical | - | -
1 | J8 | THD-20-R | Connector_PinHeader_2.54mm:PinHeader_2x20_P2.54mm_Vertical | PinHeader_2x20_P2.54mm_Vertical | THD-20-R
 |  |  |  |  |  |  |  |  |  |  |  | SUMA | 47.039920000000002
1 | CP1 | 10uF | Capacitor_Tantalum_SMD:CP_EIA-3528-21_Kemet-B_HandSolder | Tantalum, Kemet-B, 10uF@35V min. | - |  |  |  |  | 0 | -
2 | CP2,CP3 | 22uF | Capacitor_Tantalum_SMD:CP_EIA-3528-21_Kemet-B_HandSolder | Tantalum, Kemet-B, 22uF@10V min. | - |  |  |  |  | 1.643 | TAJB226K016R
1 | C3 | 100uF | Capacitor_Tantalum_SMD:CP_EIA-7343-31_Kemet-D | Kemet-D, 10V | - |  |  |  |  | 2.2789999999999999 | TAJD106K035R
2 | D1,D3 | LED Red | LED_SMD:LED_0603_1608Metric | Red 620nm LED Indication - Discrete 2.2V 2-SMD, No Lead | SML-A12U8TT86Q |  |  | 1.65 | 3434715 | 0 | -
1 | D2 | LED Green | LED_SMD:LED_0603_1608Metric | Green 572nm LED Indication - Discrete 2.2V 2-SMD, No Lead | SML-A12M8TT86N |  |  | 1.64 | 3434712 | 0 | -
2 | J5,J16 | Conn_01x22_Female | CM5IO:Hirose_FH12-22S-0.5SH_1x22-1MP_P0.50mm_Horizontal | 22 Position FFC, FPC Connector Contacts, Bottom 0.020" (0.50mm) Surface Mount, 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 | FH12-22S-0.5SH55 |  |  | 7.17 | 2300373 | 0 | -
1 | J7 | Micro_SD_Card_Det | CM5IO:SDCARD_MOLEX_503398-1892 | 9 (8 + 1) Position Card Connector microSDâ„¢ Surface Mount, Right Angle Gold | 503398-1892 |  |  |  |  | 8.41 | MX-503398-1892 | Not necessary, if no SD card is used
1 | J11 | USB_C_Receptacle_USB2.0 | Connector_USB:USB_C_Receptacle_GCT_USB4105-xx-A_16P_TopMnt_Horizontal | USBC USB2 data and power connector | USBF31-0171 |  |  |  |  | 2.5779999999999998 | UBC-RA-TF* | * - equivalent
1 | J12 | USB3_A | Connector_USB:USB3_A_Molex_48393-001 | USB 3.0 A connector | 48393-0003 |  |  |  |  | 9.67 | MX-48393-0003
1 | J14 | JST_SHBM04B-SRSS-TB | Connector_JST:JST_SH_BM04B-SRSS-TB_1x04-1MP_P1.00mm_Vertical | 4 pin vertical 1mm pitch connector | SHBM04B-SRSS-TB |  |  |  |  | 1.4419999999999999 | SM04B-SRSS-TB
1 | J22 | 46765-1301 | CM5IO:CONN_467651301_MOL | 0.40mm Pitch Micro HDMI Connector, Right-Angle Receptacle, Surface Mount, with 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 | 46765-1301 |  |  | 8.82 | 2614867 | 0 | -
1 | LP1 | 3.6uH | Inductor_SMD:L_Bourns-SRN8040_8x8.15mm | - | SRN8040HA-3R6M |  |  | 2.52 | 4216300 | 0 | -
2 | Module1 | ComputeModule5-CM5 | CM5IO:Raspberry-Pi-5-Compute-Module | 100 Position Connector Receptacle, Center Strip Contacts Surface Mount Gold | 10164227-1001A1RLF | 0 | - | 7.43 | 4137104 | 0 | -
1 | SW1 | Right angle Tact button | Button_Switch_SMD:SW_Push_1P1T_NO_CK_KMR2 | - | KMR221G LFS |  |  |  |  | 1.0469999999999999 | KMR221GLFS
1 | U6 | AP22653W6 | Package_TO_SOT_SMD:SOT-23-6 | Power Switch/Driver 1:1 P-Channel 2.1A SOT-23-6 | AP22653W6 |  |  |  |  | 1.45 | AP22653W6-7
1 | U12 | RT9742SNGV | Package_TO_SOT_SMD:TSOT-23_HandSoldering | Power Switch/Driver 1:1 N-Channel 500mA SOT-23-3 | RT9742SNGV |  |  | 1.5 | 2575555 | 0 | -
1 | U18 | RT9742GGJ5 | Package_TO_SOT_SMD:SOT-23-5 | Power Switch/Driver 1:1 N-Channel 1A TSOT-23-5 | RT9742GGJ5 |  |  | 0 | - | 0 | - | Not necessary, if no SD card is used
1 | UP1 | AP64501SP-13 | CM5IO:SOP_AP64501SP-13_DIO | - | AP64501SP-13 |  |  |  |  | 7.11 | AP64501SP-13
 |  |  |  |  |  |  |  | 46.980000000000004 | SUMA / płytka | 37.271999999999998 | SUMA / płytka

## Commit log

2025-11-19 init
2026-01-16 whatever
2026-01-16 move bottom board into CM5IO
2026-01-16 Add MIT License to the project
2026-01-17 small fixes for ground planes, logo added, minor other changes
2026-01-19 update impedance calcs
2026-01-20 post-review fixes
2026-01-20 regenerate gerber files
2026-01-20 add the fan connector back
2026-01-21 add upper board draft
2026-01-22 post-reveiw fixes
2026-01-22 final changes before ordering the design
2026-01-22 redesigning upper board
2026-01-22 top board wip
2026-01-27 DRC fixes after changing via size. fixed too small cap in PSU.
2026-01-27 add BOM
2026-01-28 Add PCIe connector. Fix some clearance violations.
2026-01-29 upper board finished (I hope)
2026-01-29 minor aesthetic changes
